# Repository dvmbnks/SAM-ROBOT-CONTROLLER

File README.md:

# SAM-ROBOT-CONTROLLER
This versatile printed circuit board is designed to seamlessly integrate and control various robot parts, providing a centralized hub for efficient and precise robotics operation. Whether you're into building robotic arms, drones, or other automated wonders, this PCB (With Arduino Nano) is your go-to solution.

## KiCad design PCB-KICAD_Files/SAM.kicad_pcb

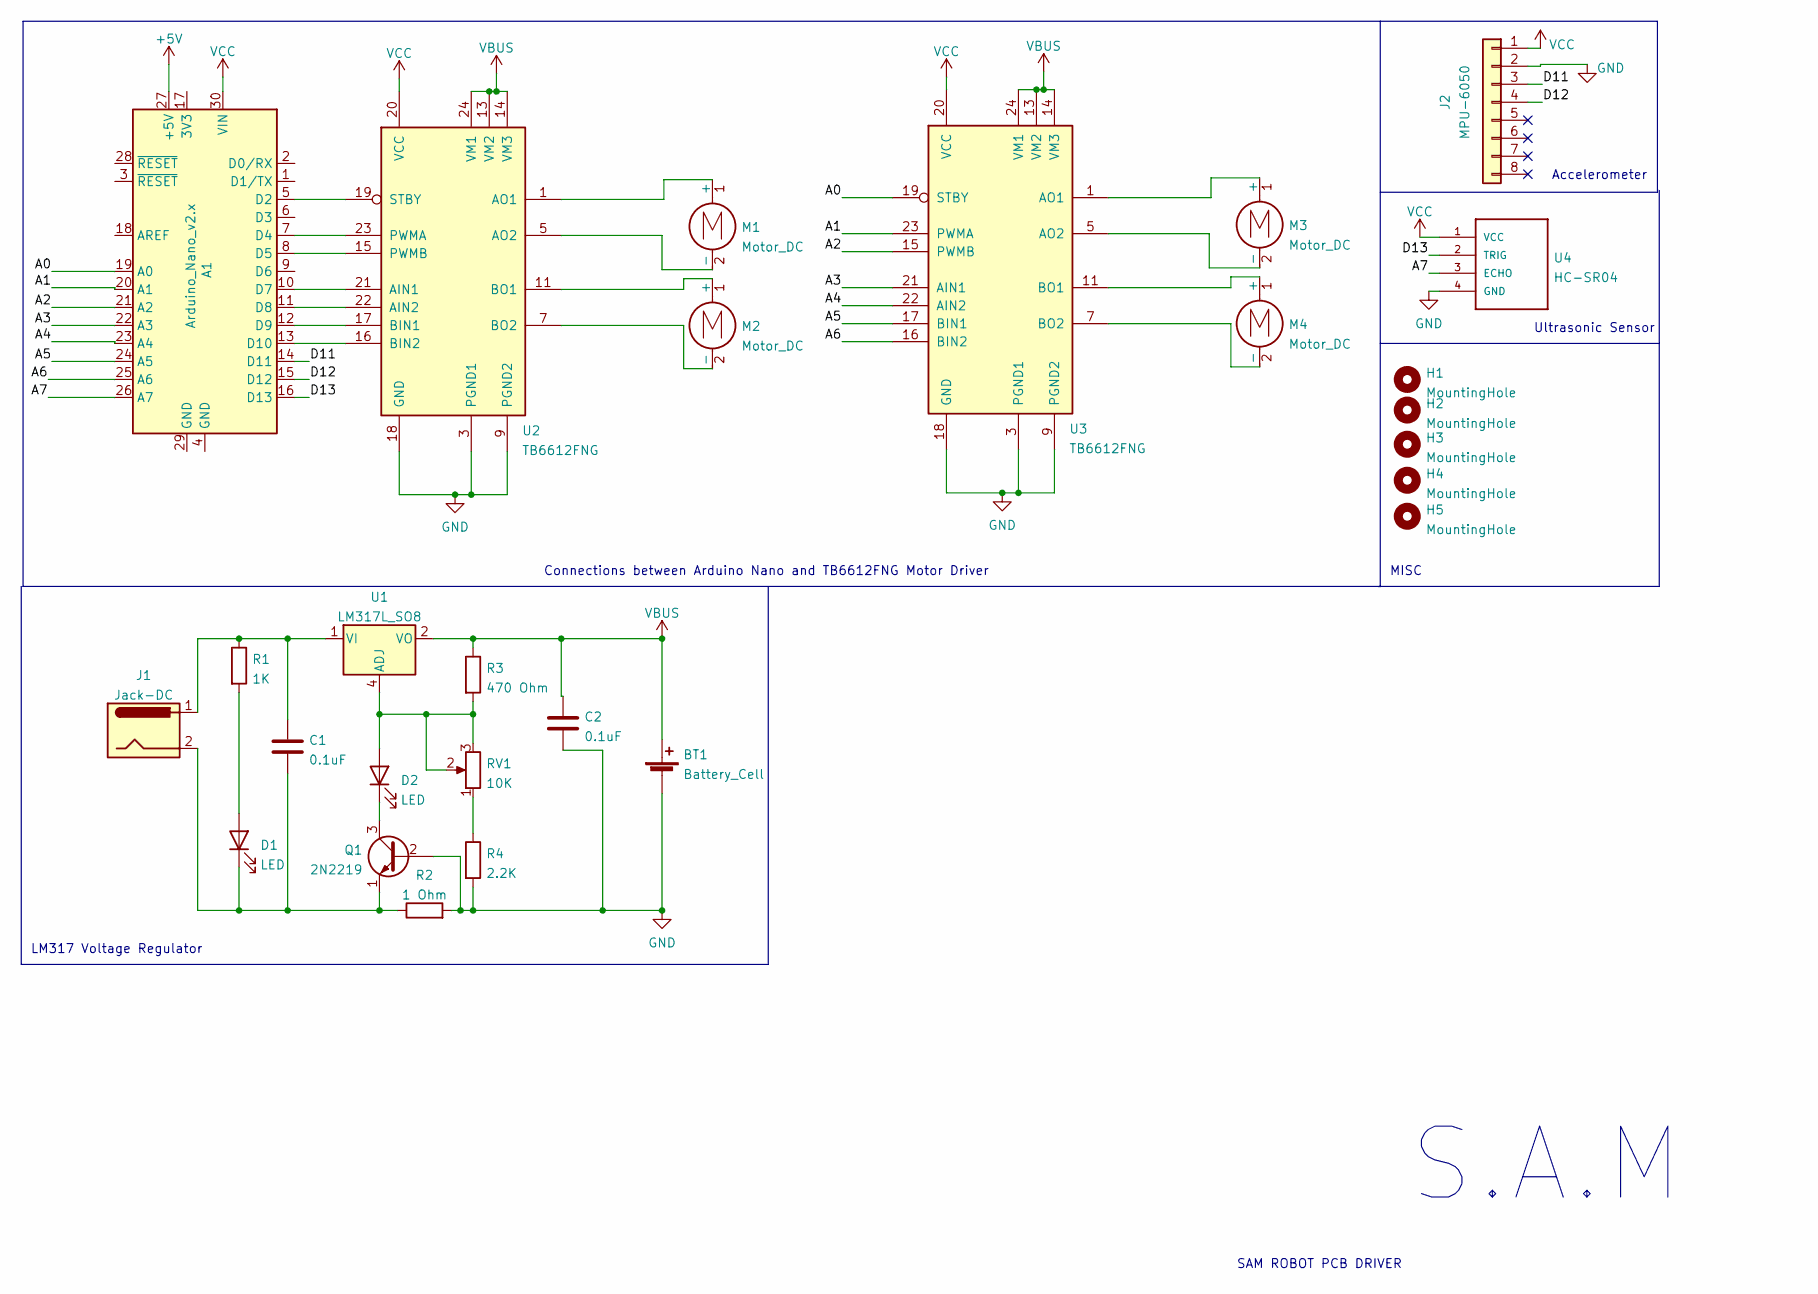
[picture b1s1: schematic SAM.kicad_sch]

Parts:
A1: Arduino_Nano_v2.x; Arduino_Nano
BT1: Battery_Cell; BatteryHolder_Keystone_2468_2xAAA
C1, C2: 0.1uF; CP_Elec_3x5.3
D1, D2: LED; D_0201_0603Metric
H1, H2, H3, H4, H5: MountingHole; MountingHole_2.2mm_M2_DIN965
J1: Jack-DC; BarrelJack_CUI_PJ-063AH_Horizontal
J2: MPU-6050; PinSocket_1x08_P1.00mm_Vertical
M1, M2, M3, M4: Motor_DC; TerminalBlock_Phoenix_MKDS-1,5-2_1x02_P5.00mm_Horizontal
Q1: 2N2219; TO-39-3
R1: 1K; R_0201_0603Metric
R2: 1 Ohm; R_0201_0603Metric
R3: 470 Ohm; R_0201_0603Metric
R4: 2.2K; R_0201_0603Metric
RV1: 10K; Potentiometer_Bourns_3314G_Vertical
U1: LM317L_SO8; SOIC-8_3.9x4.9mm_P1.27mm
U2, U3: TB6612FNG; SSOP-24_5.3x8.2mm_P0.65mm
U4: HC-SR04; XCVR_HC-SR04

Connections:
+5V: A1.27 (+5V)
/A0: A1.19 (A0), U3.19 (STBY)
/A1: A1.20 (A1), U3.23 (PWMA)
/A2: A1.21 (A2), U3.15 (PWMB)
/A3: A1.22 (A3), U3.21 (AIN1)
/A4: A1.23 (A4), U3.22 (AIN2)
/A5: A1.24 (A5), U3.17 (BIN1)
/A6: A1.25 (A6), U3.16 (BIN2)
/A7: A1.26 (A7), U4.3 (ECHO)
/D11: A1.14 (D11), J2.3
/D12: A1.15 (D12), J2.4
/D13: A1.16 (D13), U4.2 (TRIG)
GND: BT1.2 (-), C2.2, J2.2, Q1.2 (B), R2.2, R4.2, U2.3 (PGND1), U2.4 (PGND1), U2.9 (PGND2), U2.10 (PGND2), U2.18 (GND), U3.3 (PGND1), U3.4 (PGND1), U3.9 (PGND2), U3.10 (PGND2), U3.18 (GND), U4.4 (GND)
unnamed: A1.5 (D2), U2.19 (STBY)
unnamed: A1.7 (D4), U2.23 (PWMA)
unnamed: A1.8 (D5), U2.15 (PWMB)
unnamed: A1.10 (D7), U2.21 (AIN1)
unnamed: A1.11 (D8), U2.22 (AIN2)
unnamed: A1.12 (D9), U2.17 (BIN1)
unnamed: A1.13 (D10), U2.16 (BIN2)
unnamed: C1.1, J1.1, R1.1, U1.1 (VI)
unnamed: C1.2, D1.1 (K), J1.2, Q1.1 (E), R2.1
unnamed: D1.2 (A), R1.2
unnamed: D2.1 (K), Q1.3 (C)
unnamed: D2.2 (A), R3.2, RV1.2, RV1.3, U1.4 (ADJ)
unnamed: M1.1 (+), U2.1 (AO1), U2.2 (AO1)
unnamed: M1.2 (-), U2.5 (AO2), U2.6 (AO2)
unnamed: M2.1 (+), U2.11 (BO1), U2.12 (BO1)
unnamed: M2.2 (-), U2.7 (BO2), U2.8 (BO2)
unnamed: M3.1 (+), U3.1 (AO1), U3.2 (AO1)
unnamed: M3.2 (-), U3.5 (AO2), U3.6 (AO2)
unnamed: M4.1 (+), U3.11 (BO1), U3.12 (BO1)
unnamed: M4.2 (-), U3.7 (BO2), U3.8 (BO2)
unnamed: R4.1, RV1.1
VBUS: BT1.1 (+), C2.1, R3.1, U1.2 (VO), U1.3 (VO), U1.6 (VO), U1.7 (VO), U2.13 (VM2), U2.14 (VM3), U2.24 (VM1), U3.13 (VM2), U3.14 (VM3), U3.24 (VM1)
VCC: A1.30 (VIN), J2.1, U2.20 (VCC), U3.20 (VCC), U4.1 (VCC)

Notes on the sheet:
Ultrasonic Sensor
Connections between Arduino Nano and TB6612FNG Motor Driver
SAM ROBOT PCB DRIVER
MISC
S.A.M
LM317 Voltage Regulator
Accelerometer

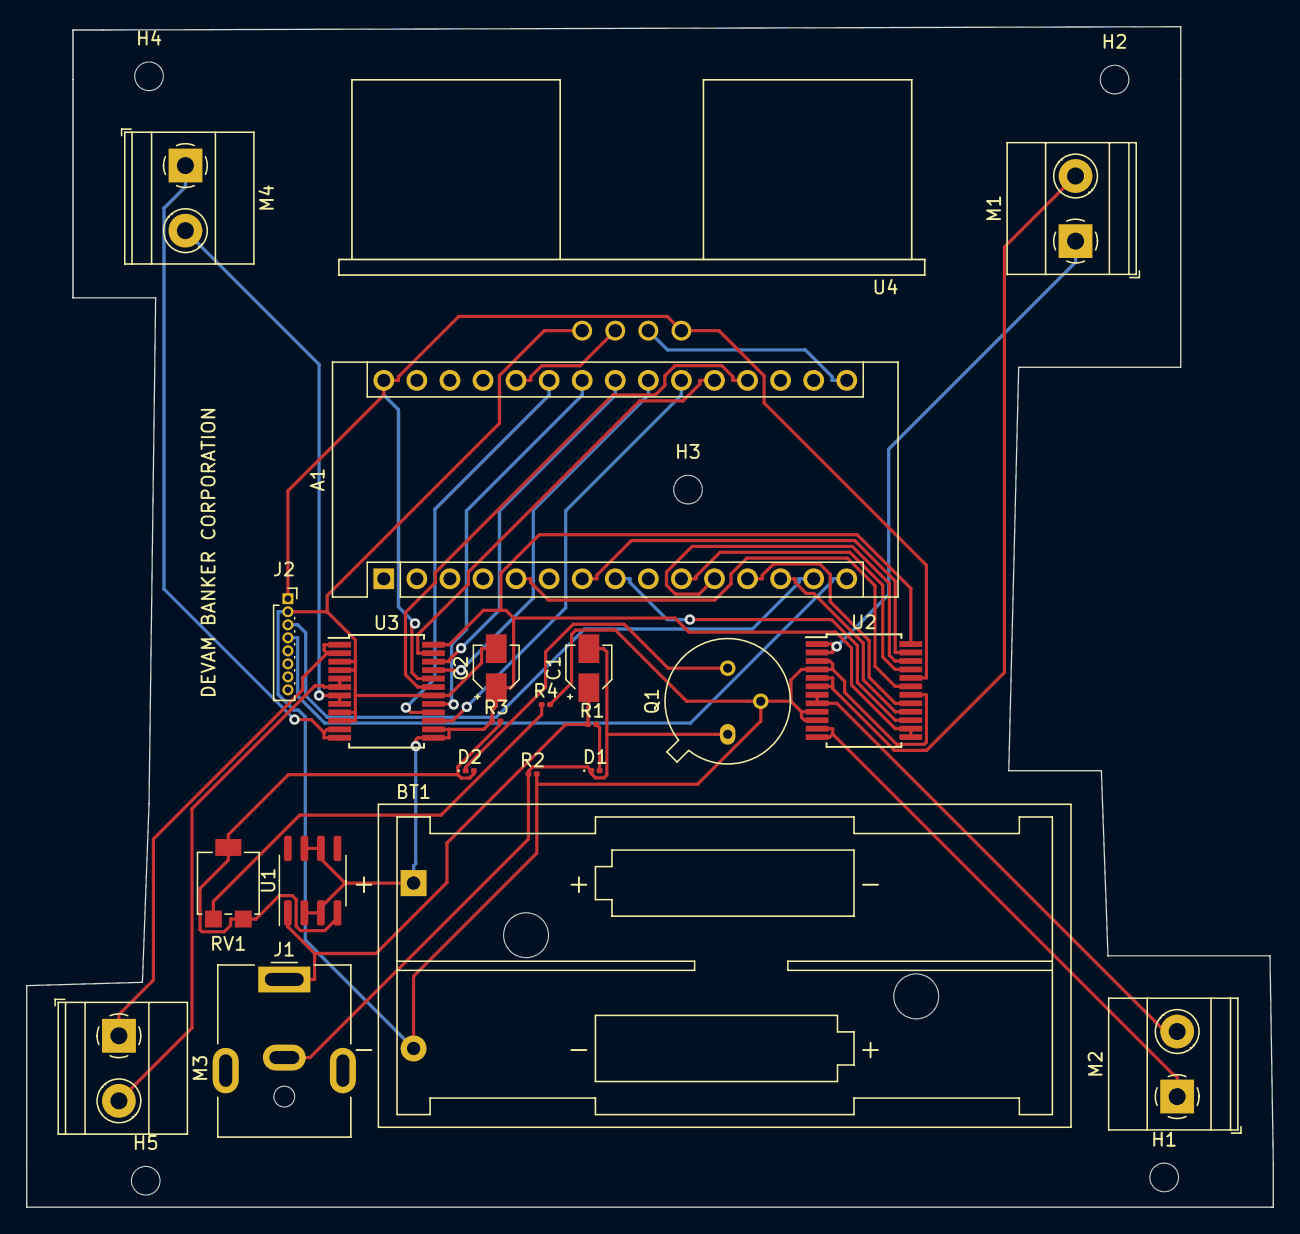
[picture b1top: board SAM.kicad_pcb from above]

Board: 2 copper layers, 95.8 x 90.7 mm, 27 parts (0 on the bottom side), 35 nets.

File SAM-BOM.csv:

"Source:","C:\Users\Devam Banker\Google Drive\Personal\Projects\Main Projects\SAM\SAM.kicad_sch"
"Date:","12/7/2022 3:24:53 PM"
"Tool:","Eeschema (6.0.1)"
"Generator:","E:\Softwares\New folder\6.0\bin\scripting\plugins/bom_csv_grouped_by_value.py"
"Component Count:","22"

"Individual Components:"

"Item","Qty","Reference(s)","Value","LibPart","Footprint","Datasheet","MANUFACTURER"
"","","A1","Arduino_Nano_v2.x","MCU_Module:Arduino_Nano_v2.x","Module:Arduino_Nano","https://www.arduino.cc/en/uploads/Main/ArduinoNanoManual23.pdf",""
"","","BT1","Battery_Cell","Device:Battery_Cell","Battery:BatteryHolder_Keystone_2468_2xAAA","~",""
"","","C1","0.1uF","Device:C","Capacitor_SMD:CP_Elec_3x5.3","~",""
"","","C2","0.1uF","Device:C","Capacitor_SMD:CP_Elec_3x5.3","~",""
"","","D1","LED","Device:LED","Diode_SMD:D_0201_0603Metric","~",""
"","","D2","LED","Device:LED","Diode_SMD:D_0201_0603Metric","~",""
"","","J1","Jack-DC","Connector:Jack-DC","Connector_BarrelJack:BarrelJack_CUI_PJ-063AH_Horizontal","~",""
"","","J2","MPU-6050","Connector_Generic:Conn_01x08","Connector_PinSocket_1.00mm:PinSocket_1x08_P1.00mm_Vertical","~",""
"","","M1","Motor_DC","Motor:Motor_DC","TerminalBlock_Phoenix:TerminalBlock_Phoenix_MKDS-1,5-2_1x02_P5.00mm_Horizontal","~",""
"","","M2","Motor_DC","Motor:Motor_DC","TerminalBlock_Phoenix:TerminalBlock_Phoenix_MKDS-1,5-2_1x02_P5.00mm_Horizontal","~",""
"","","M3","Motor_DC","Motor:Motor_DC","TerminalBlock_Phoenix:TerminalBlock_Phoenix_MKDS-1,5-2_1x02_P5.00mm_Horizontal","~",""
"","","M4","Motor_DC","Motor:Motor_DC","TerminalBlock_Phoenix:TerminalBlock_Phoenix_MKDS-1,5-2_1x02_P5.00mm_Horizontal","~",""
"","","Q1","2N2219","Transistor_BJT:2N2219","Package_TO_SOT_THT:TO-39-3","http://www.onsemi.com/pub_link/Collateral/2N2219-D.PDF",""
"","","R1","1K","Device:R","Resistor_SMD:R_0201_0603Metric","~",""
"","","R2","1 Ohm","Device:R","Resistor_SMD:R_0201_0603Metric","~",""
"","","R3","470 Ohm","Device:R","Resistor_SMD:R_0201_0603Metric","~",""
"","","R4","2.2K","Device:R","Resistor_SMD:R_0201_0603Metric","~",""
"","","RV1","10K","Device:R_Potentiometer","Potentiometer_SMD:Potentiometer_Bourns_3314G_Vertical","~",""
"","","U1","LM317L_SO8","Regulator_Linear:LM317L_SO8","Package_SO:SOIC-8_3.9x4.9mm_P1.27mm","http://www.ti.com/lit/ds/snvs775k/snvs775k.pdf",""
"","","U2","TB6612FNG","Driver_Motor:TB6612FNG","Package_SO:SSOP-24_5.3x8.2mm_P0.65mm","https://toshiba.semicon-storage.com/us/product/linear/motord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",""
"","","U3","TB6612FNG","Driver_Motor:TB6612FNG","Package_SO:SSOP-24_5.3x8.2mm_P0.65mm","https://toshiba.semicon-storage.com/us/product/linear/motord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",""
"","","U4","HC-SR04","HC-SR04:HC-SR04","HC-SR04:XCVR_HC-SR04","","Osepp"



"Collated Components:"

"Item","Qty","Reference(s)","Value","LibPart","Footprint","Datasheet","MANUFACTURER"
"1","1","A1","Arduino_Nano_v2.x","MCU_Module:Arduino_Nano_v2.x","Module:Arduino_Nano","https://www.arduino.cc/en/uploads/Main/ArduinoNanoManual23.pdf",""
"2","1","BT1","Battery_Cell","Device:Battery_Cell","Battery:BatteryHolder_Keystone_2468_2xAAA","~",""
"3","2","C1, C2","0.1uF","Device:C","Capacitor_SMD:CP_Elec_3x5.3","~",""
"4","2","D1, D2","LED","Device:LED","Diode_SMD:D_0201_0603Metric","~",""
"5","1","J1","Jack-DC","Connector:Jack-DC","Connector_BarrelJack:BarrelJack_CUI_PJ-063AH_Horizontal","~",""
"6","1","J2","MPU-6050","Connector_Generic:Conn_01x08","Connector_PinSocket_1.00mm:PinSocket_1x08_P1.00mm_Vertical","~",""
"7","4","M1, M2, M3, M4","Motor_DC","Motor:Motor_DC","TerminalBlock_Phoenix:TerminalBlock_Phoenix_MKDS-1,5-2_1x02_P5.00mm_Horizontal","~",""
"8","1","Q1","2N2219","Transistor_BJT:2N2219","Package_TO_SOT_THT:TO-39-3","http://www.onsemi.com/pub_link/Collateral/2N2219-D.PDF",""
"9","1","R1","1K","Device:R","Resistor_SMD:R_0201_0603Metric","~",""
"10","1","R2","1 Ohm","Device:R","Resistor_SMD:R_0201_0603Metric","~",""
"11","1","R3","470 Ohm","Device:R","Resistor_SMD:R_0201_0603Metric","~",""
"12","1","R4","2.2K","Device:R","Resistor_SMD:R_0201_0603Metric","~",""
"13","1","RV1","10K","Device:R_Potentiometer","Potentiometer_SMD:Potentiometer_Bourns_3314G_Vertical","~",""
"14","1","U1","LM317L_SO8","Regulator_Linear:LM317L_SO8","Package_SO:SOIC-8_3.9x4.9mm_P1.27mm","http://www.ti.com/lit/ds/snvs775k/snvs775k.pdf",""
"15","2","U2, U3","TB6612FNG","Driver_Motor:TB6612FNG","Package_SO:SSOP-24_5.3x8.2mm_P0.65mm","https://toshiba.semicon-storage.com/us/product/linear/motord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",""
"16","1","U4","HC-SR04","HC-SR04:HC-SR04","HC-SR04:XCVR_HC-SR04","","Osepp"
